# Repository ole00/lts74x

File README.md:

# lts74x
Yet another 74x-series IC logic tester that uses Arduino board for testing the logic states of the IC.

Lts74x was inspired by the following propjects:
* Integrated circuit tester: https://github.com/Johnlon/integrated-circuit-tester
* Smart IC Tester: https://github.com/akshaybaweja/Smart-IC-Tester

Features:
* Uses Arduino Nano and one GPIO Expander IC
* Tests many 16 and 18 pin 74x series ICs, test database is based on the above projects.
* Tests some 20 pin 74x series ICs, requires Arduino Nano modification (LED and pull resistor removals)
* Uses OLED screen for IC selection
* Displays basic IC pinout and indicates failed pins after the test.
* Screen saver to prevent OLED screen burn.
* Supports testing Z states on IC pins.
* Supports Clock pin.
* Supports latched pin testing.
* Tests are compressed to fit into Arduino Nano flash (still about ~4 kb free).
* Open source / hardware design (kicad), schematics and gerbers provided.
* Basic Arduino pin protection via 1k Ohm resitor in series (we test ICs that might be broken internally).

Setup:
-----------
 * Upload the lts74x20.ino sketch to your Arduino Nano. Use Arduino IDE to upload the sketch, both IDE version 1.8.X and 2.X should work fine.
   Note that some USB-C based Arduino Nano clones require to select Tools-> Processor ->ATMegae328P (Old Bootloader) to flash them.
 * Decide whether you want/need the 20pin IC test feature. If so, modify the Arduino board - see Arduino mod in Q&A section.
 * Build the lts74x hardware. Buy the PCB from an online PCB production service (use provided gerber archive in 'gerbers' directory).
   Then solder the components on the PCB - check the schematic (lts74x.pdf) and bom.txt for parts list.

How lts74x works:
------------------
* The IC tester works on it own, that means it does not need a PC serial connection in order to test the IC chips.
* After start, the IC list is displayed on the screen and you can select the IC you want to test by pressing
 Up and Down buttons. Selection is confirmed by the OK button. You can also check the basic pinout of the device
 by pressing the Back button.
* Pressing the OK button starts the IC testing (the switch powering the IC must be switched on - the app dectects
 that and asks you to flip the switch if the switch is Off). Of course, you should insert the actual IC in the ZIF
 socket beforehand to get meaningful test results. Insert the IC while the power switch is Off (which prevents accidental zapping of
 the IC during insertion), then you can turn the Power switch On and start the test.

* Each IC has its own set of tests stored in the flash. Upon pressing OK, the test set is loaded, decoded and then run 100 times.
  Note that the test set is comprised of several individual tests that check the different input pin combinations (High, Low inputs)
  and output results (High, Low, Z state outputs). The whole testing set is run and if there is an error the IC pinout with
  failed pins is displayed on the screen.

* Each test is defined as a text string where each character in the string corresponds to a certain pin state. Pins marked as 0 or 1
  are the IC input pins and their value is set via Arduino to the desired value (Low or High repsectively). Pins marked
  as L, H or Z are the IC output pins and their value is read by Arduino and evaluated. L marked pins must read digital 0, H marked
  pins must read digital 1 from the correspondig GPIO. Z marked pins test the high impedance output (see Q&A section for details) 
  of the IC chip.
  
PCB:
-----------
 The most convenient way to get the PCB is to order it online on jlcpcb.com, pcbway.com, allpcb.com or other online services. 
 Use the zip archive stored in the gerbers directory and upload it to the manufacturer's site of your choice. 
 Upload the lts74x_r3_fab.zip and set the following parameters (if required).

  * Dimensions are 85x68 mm
  * 2 layer board
  * PCB Thickness: 1.6, or 1.2 mm
  * Copper Weight: 1
  * The rest of the options can stay default or choose whatever you fancy (colors, finish etc.)

Soldering/assembly steps:
--------------------------
  * start with the smallest parts, solder the resistors and capacitors.
  * Use multimeter and verify the resistance between Arduino pins and GND (Test point TP1). It should be ~ 470kOhm.
  * Use multimeter and verify the resistance between Arduino pins the corresponding ZIF socket pin - It should be 1kOhm. 
  * To do the above, check the schematics PDF to find out which Arduino pins lead to which ZIF socket pin.
  * solder the U1 IC. 
  * solder the  Q1 and Q2 Mosfets. Note that there is a dual footprint for the Mosfets, use either Through-Hole footrpint or SMT fotrpint, but not
    both at the same time.  Important: use low soldering temeprature (no more that 280 C)
    to prevent the Mosfet damage. While soldering, touch the Mosfets pins for only a very short time (2 seconds max). If you need
    to improve the soldering joint, let the Mosfet to cool down a bit, apply a flux on the pin and then briefly touch upon the pin with the soldering tip.
    I managed to burn 2 Mosfets while doing so with higher temperature. To test the Mosfet is OK use multimeter and test resistance between Ground pin
    (Source) and the Drain pin while the board in powered off. The resistance value must be ~ 470kOhm. If it is way less than that (like 2kOhm) 
    the Mosfet gate was damaged during soldering.
  * Solder the LED
  * Solder the power switch
  * Test your OLED display on a breadboard connected to Arduino and a test sketch whether the display actually works.
    I got an LCD delivered which was faulty, so I had to use another one. Returning a faulty OLED display to the seller might be problematic
    if there are traces of soldering on the display. While running the OLED test, check which I2C address it uses.
  * Solder the OLED display. Before you do that, use M2 bolt and nuts to secure the display to the PCB. Use extra M2 nuts in between the OLED display
    and and the tester PCB as a spacer.
  * Solder the buttons
  * Optionally, solder the Arduino female header socket on the tester PCB if you want to have your Arduino Nano detachable.
  * Optionally, mod your Arduino Nano to support 20 pin IC testing capability (see Q&A section).
  * Verify the 5V pin and Ground is not shorted - use multimeter and continuity test to do that. Very short initial beep might be OK as that
    might be the decoupling capacitors letting through the probing current.
  * Insert/solder the Arduino Uno.
  * Power the Board on by plugging-in the USB cable. Test the basic functionality (buttons, power switch and LED, test an IC with no IC inserted/used).
    If they do not work, check the troubleshooting.

  * Solder the ZIF socket.

Q&A:
---------------
* I can't upload the sketch to my my Arduino Nano clone because of a communication error
   - Nano clones often use CH340 serial chip (or in my case, a clone of the CH340 chip). When using Windows or Mac,
     make sure you have the CH340 serial driver installed. See : https://learn.sparkfun.com/tutorials/how-to-install-ch340-drivers/all
   - Ensure Arduino Nano is selected in the Arduino IDE: Tools -> Board: Arduino Nano
   - Try setting the Processor option Old Bootloader: Tools-> Processor ->ATMega328P (Old Bootloader)

* I turned it on and the OLED display does not show anything
   - Ensure lts74x20.ino sketch was uploaded to your Arduino Nano.
   - Did you do the OLED test as described in Assembly steps? Check the OLED screen communicates via I2C 
     by running I2C scanner sketch: File -> Examples -> Wire -> i2c_scanner. It should find 2 devices:
     one is the GPIO Expander address 0x18 and the second one is the OLED screen using address 0x78.
     Modify OLED_ADDRESS value in lts74x20.ino sketch if your OLED address is different.

* what is the On switch used for? When do I use it?

    - Normally, the switch should be in the Off position (LED is not lit). Also when insering the IC chip or when removing the IC chip
      from the ZIF socket the switch should be Off. Just before you start the test the switch should be turned On.
      So in general: insert the IC when the switch is Off, then turn the switch On and run the test. When finished turn the switch Off,
      and remove the IC chip from the socket.

* I tested a brand new IC chip and it fails during the test. Some pins (or a single pin) indicate a failure.
    - Double check all resistors leading to the ZIF socket pins (1 kOhm) and weak pull down resistors (470 kOhm) are well soldered.
     There might be a missing solder joint on that particular pin or on a pin that contributes to the logical output of the failed pin.
     Test the resistance by attaching multimeter probes to an Arduin pin and corresponding ZIF socket pin, and also between
     the Arduino pin and ground (TP1).

* The site image on the very top shows some bodge wires connected to U1 - shall I be concerned?
  - No, there is no need to replicate that on your board. The image shows a prototype board (Revision 2) that has a bug which was fixed in 
    board Revision 3. Rev. 3 is currently the one available for download.
  
* What is the mod to let me test 20 pin ICs?
    - See image bellow. Basically, remove few pull resistors (marked red on the bellow image) by touching them with a hot soldering iron (~350C) for 4 seconds and then
      while pushing them a bit sideways they will slide-off of its footprints on the PCB.
      **Important:** before doing the mod make sure the Arduino sketch is uploaded. After the mod is done, it won't be possible to upload the sketch
      via USB. Uploading will be possible, but it is less convenient and requires another Arduino board.
    - remove the RX and TX resistors or LEDs on the top. 
    - remove the L resistor or LED on the top
    - remove the resistors on the bottom of the board. Please note that my Arduino nano is a clone, it does not even use a genuine CH340
       serial chip. If you have a different Arduino Nano board than the one pictured bellow, then you may need to remove other resistors
       or it might be more convenient to remove the serial chip itself.
    - solder headers to allow sketch reprogramming in the future (marked green on the bellow image)

* How is the Z state stested?
    - The Z - or High impedance - state test is based on 2 following facts: 
    - The lts74x circuit has very weak external pull down resistors (470k Ohm) on all ZIF pins. During testing of High or Low states this pull down resistor
      does not affect the results read from the pins, because IC currents are much stronger.
    - The IC pin in Z state should not source or sink any current from the wire connected to the pin (if it does, it is an error).
     Therefore the pin's current (if there is any teeny tiny one) should not have enough 'strength' to override the actual state of the wire
     leading to the pin. So, if the Arduino sets a pin leading to the IC's Z pin as Input with internall Pull up (~30k Ohm), then Arduino should 
     read it as High. Also, if Arduino sets a pin leading to the IC's Z pin as Input (external pull down, see above) then Arduino should
     read it as Low. If the reeading is incorrect then the IC's pin is not in the Z state as it 'overrides' the pull resistors by sinking or 
     sourcing the current. That means it's not in Z state and the pin is malfunctioning or is damaged. The Z test does exactly that:
     sets the pin as Input with internal pull up and reads the value, then sets it as Input with external pull down and reads the value.
     If the read values are correct the pin is in Z state. There are few more details involved in the actuall Z test (like there must be a small
     delay allowing the pull resistor to react before reading the value etc.), so check the source code if you are interested.

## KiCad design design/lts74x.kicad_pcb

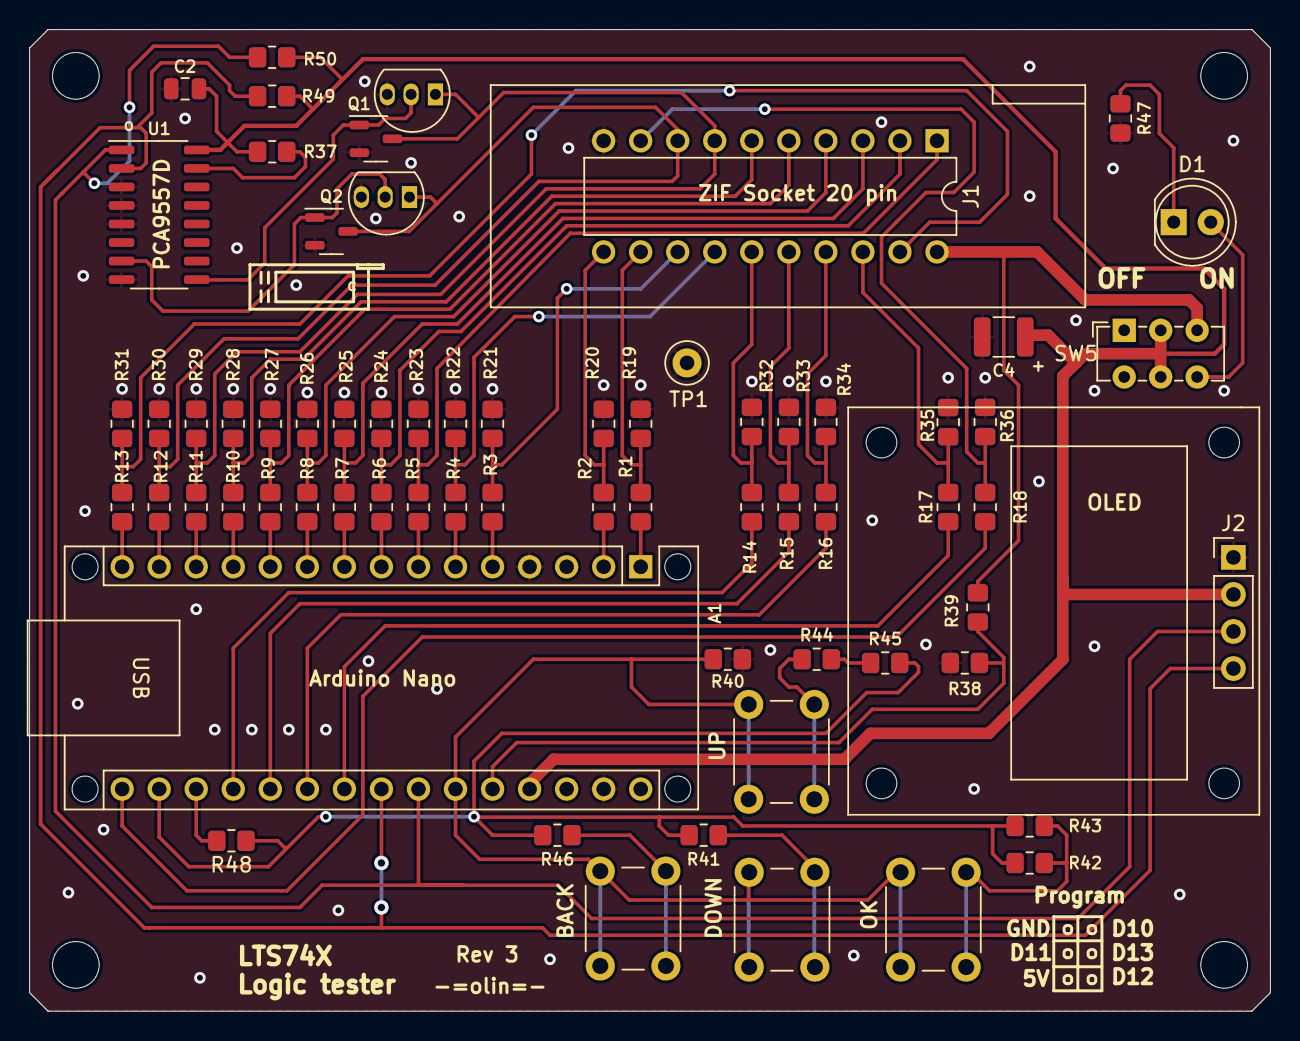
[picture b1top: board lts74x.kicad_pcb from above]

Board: 2 copper layers, 85.1 x 67.3 mm, 75 parts (0 on the bottom side), 55 nets.

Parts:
A1: Arduino_Nano_v3.x; Arduino_Nano_WithMountingHoles
C2: 0.1u; C_0805_2012Metric
C4: 22u; C_1210_3225Metric
D1: LED; LED_D5.0mm
H1, H2, H3, H4: MountingHole; MountingHole_3.2mm_M3
H5, H6, H7, H8: MountingHole; MountingHole_2.1mm
J1: ZIF Socket; DIP-20_W7.62mm
J2: OLED SSD1306; PinHeader_1x04_P2.54mm_Vertical
Q1, Q2#2: N_MOS; SOT-23-3
Q1#2, Q2: TO-92L_Inline
R1, R2, R3, R4, R5, R6, R7, R8, R9, R10, R11, R12, R13, R14, R15, R16, R17, R18, R47: 1k; R_0805_2012Metric_Pad1.20x1.40mm_HandSolder
R19, R20, R21, R22, R23, R24, R25, R26, R27, R28, R29, R30, R31, R32, R33, R34, R35, R36: 470k; R_0805_2012Metric_Pad1.20x1.40mm_HandSolder
R37, R38, R39, R40, R41, R42, R43, R44, R45, R49, R50: 10k; R_0805_2012Metric_Pad1.20x1.40mm_HandSolder
R46, R48: 2k2; R_0805_2012Metric_Pad1.20x1.40mm_HandSolder
SW1: OK (2V2); SW_PUSH_6mm
SW2: Down (1V6); SW_PUSH_6mm
SW3: Up (1V1); SW_PUSH_6mm
SW4: Back (2V7); SW_PUSH_6mm
SW5: SW_Push_DPDT; SW_E-Switch_EG1271_SPDT
TP1: TestPoint_Small; TestPoint_Loop_D2.50mm_Drill1.0mm
U1: PCA9557D; SO-16_3.9x9.9mm_P1.27mm

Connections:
3V3: A1.17 (3V3), R41.2, R42.2, R43.2, R45.2, R46.2, R48.1
5V: A1.27 (+5V), C2.1, C4.1, J2.2, R37.2, R49.1, R50.1, SW5.2 (B), SW5.5 (B), U1.16 (VDD)
5V_SW: J1.20, R39.1, SW5.3 (C)
GND: A1.4 (GND), A1.29 (GND), C2.2, C4.2, J1.10, J2.1, Q1.2, Q1#2.3, Q2.3, Q2#2.2, R19.1, R20.1, R21.1, R22.1, R23.1, R24.1, R25.1, R26.1, R27.1, R28.1, R29.1, R30.1, R31.1, R32.1, R33.1, R34.1, R35.1, R36.1, R38.1, R40.1, R47.2, TP1.1, U1.3 (A0), U1.4 (A1), U1.5 (A2), U1.8 (VSS)
KEYB: A1.25 (A6), R40.2, SW1.1, SW2.1, SW3.1, SW4.1
unnamed: A1.19 (A0), R14.2
unnamed: A1.20 (A1), R15.2
unnamed: A1.21 (A2), R16.2
unnamed: A1.22 (A3), R17.2
unnamed: A1.26 (A7), R38.2, R39.2
unnamed: A1.18 (AREF), R48.2
unnamed: A1.2 (D0/RX), R2.2
unnamed: A1.1 (D1/TX), R1.2
unnamed: A1.5 (D2), R3.2
unnamed: A1.6 (D3), R4.2
unnamed: A1.7 (D4), R5.2
unnamed: A1.8 (D5), R6.2
unnamed: A1.9 (D6), R7.2
unnamed: A1.10 (D7), R8.2
unnamed: A1.11 (D8), R9.2
unnamed: A1.12 (D9), R10.2
unnamed: A1.13 (D10), R11.2
unnamed: A1.14 (D11), R12.2
unnamed: A1.15 (D12), R13.2
unnamed: A1.16 (D13), R18.2
unnamed: D1.2 (A), SW5.6 (C)
unnamed: D1.1 (K), R47.1
unnamed: R41.1, SW2.2
unnamed: R42.1, R43.1, SW1.2
unnamed: R44.1, SW3.2
unnamed: R44.2, R45.1
unnamed: R46.1, SW4.2
unnamed: R37.1, U1.15 (~RESET)
SCL: A1.24 (A5), J2.3, R50.2, U1.1 (SCL)
SDA: A1.23 (A4), J2.4, R49.2, U1.2 (SDA)
ZIF1: J1.1, R5.1, R23.2
ZIF2: J1.2, R6.1, R24.2
ZIF3: J1.3, R7.1, R25.2
ZIF4: J1.4, R8.1, R26.2
ZIF5: J1.5, R9.1, R27.2
ZIF6: J1.6, R10.1, R28.2
ZIF7: J1.7, Q1.3, Q1#2.1, R11.1, R29.2
ZIF8: J1.8, Q2.1, Q2#2.3, R12.1, R30.2
ZIF9: J1.9, R18.1, R36.2
ZIF11: J1.11, R2.1, R20.2
ZIF12: J1.12, R1.1, R19.2
ZIF13: J1.13, R3.1, R21.2
ZIF14: J1.14, R4.1, R22.2
ZIF15: J1.15, R14.1, R32.2
ZIF16: J1.16, R15.1, R33.2
ZIF17: J1.17, R16.1, R34.2
ZIF18: J1.18, R17.1, R35.2
ZIF19: J1.19, R13.1, R31.2
ZIF_G7: Q1.1, Q1#2.2, U1.9 (IO2)
ZIF_G8: Q2.2, Q2#2.1, U1.7 (IO1)

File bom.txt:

BOM for lts74x rev 3
--------------------------------------------------------------------------------
"Item","Qty","Reference(s)","info"

"1","1","A1","Arduino_Nano_v3.x","http://www.mouser.com/pdfdocs/Gravitech_Arduino_Nano3_0.pdf"
"2","1","C2","0.1u -  Capacitor_SMD:C_0805_2012Metric"
"3","1","C4","22u - Capacitor_SMD:C_1210_3225Metric"
"4","1","D1","LED","LED_THT:LED_D5.0mm"
"5","1","J1","ZIF Socket 02x10 narrow 2.54mm pin pitch Package_DIP:DIP-20_W7.62mm"
"6","1","J2","OLED SSD1306 Connector_PinHeader_2.54mm"
"7","2","Q1, Q2","N_MOSFET Enhancement Package_TO_SOT_SMD:SOT-23-3 Any N mosfet enhancement with low-ish RDS On value"
"8","19","R1, R2, R3, R4, R5, R6, R7, R8, R9, R10, R11, R12, R13, R14, R15, R16, R17, R18, R47","1k","Resistor_SMD:R_0805_2012Metric"
"9","18","R19, R20, R21, R22, R23, R24, R25, R26, R27, R28, R29, R30, R31, R32, R33, R34, R35, R36","470k","Resistor_SMD:R_0805_2012Metric"
"10","11","R37, R38, R39, R40, R41, R42, R43, R44, R45, R49, R50","10k","Resistor_SMD:R_0805_2012Metric"
"11","2","R46, R48","2k2","Resistor_SMD:R_0805_2012Metric"
"12","4","SW1, SW2, SW3, SW4","Button_Switch_THT:SW_PUSH_6mm"
"13","1","SW5","SW_Push_DPDT - Button_Switch_THT EG1271_SPDT"
"14","1","U1","PCA9557D","GPIO expander Package_SO:SO-16_3.9x9.9mm_P1.27mm","https://www.nxp.com/docs/en/data-sheet/PCA9557.pdf"

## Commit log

2023-06-23 Initial Arduino code, Kicad design, schematic and gerbers.
2023-06-23 Created README.md
2023-06-24 added top image
2023-07-23 img: added Arduino Nano image with the serial mod
2023-07-23 Update README.md
    added link to the Arduino Nano mods image
2023-07-23 Update README.md
    fixed typos
2023-07-23 added bom.txt
2024-03-09 Update README.md: typos and clarity
2024-03-09 Update README.md: fixed typo
